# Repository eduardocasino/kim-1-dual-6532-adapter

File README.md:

# KIM-1 Dual 6530-6532 adapter

## Introduction

Welcome to the KIM-1 Dual 6530-6532 adapter repository. This adapter replaces both 6530 chips on the KIM-1 with a single board that contains a couple of 6532 chips, an EPROM and a few logic ICs.

As far as I know, this is the only board that allows you to replace both 6530 chips simultaneously.

## About

I designed this board for [my KIM-1 PCB replica](https://github.com/eduardocasino/kim-1), but it will also work with real KIM-1s that have both RRIOTs missing or broken.

The schematic is based on Ruud Baltissen's KIM-1 replica, with very minor modifications. The PCB features hand-traced tracks to seamlessly integrate with the KIM-1 board:

~~WARNING: I have not yet sent the board to fabrication, so it is untested!~~

The board has been successfully tested with my [my KIM-1 replica](https://github.com/eduardocasino/kim-1)

## Programming the EPROM

You can get the ROM contents from [Hans Otten's site](http://retro.hansotten.nl/6502-sbc/kim-1-manuals-and-software/kim_1-roms/)

There are two sets available: One that uses $00 as filler bytes and another that uses $FF. Both work equally well, but the one with $00 is what the original KIM-1 has. To program the EPROM:

1. Download "6530-002 fillerbyte00.bin" and "6530-003 fillerbyte00.bin" from Hans Otten's site (replace FF with 00 if you wish)
"6530-003 fillerbyte00.bin" has the ROM contents from $1800 to $1BFF and
"6530-002 fillerbyte00.bin" from $1C00 to $1FFF

2. Concat both files:

~~~
$ cat "6530-003 fillerbyte00.bin" "6530-002 fillerbyte00.bin" > KIM-1-ROM.bin
~~~

3. Program the EPROM with the resulting file starting at address $1800

## Licensing

This is a personal project that I am sharing in case it is of interest to any retrocomputing enthusiast and all the information in this repository is provided "as is", without warranty of any kind. I am not liable for any damages that may occur, whether it be to individuals, objects, KIM-1 computers, kittens or any other pets. It should also be noted that this design has not been tested and may contain errors, therefore anyone who chooses to use it does so at their own risk.

This work is licensed under a [Creative Commons Attribution-NonCommercial 4.0 International License](http://creativecommons.org/licenses/by-nc/4.0/).

EXCEPTION: The electrical schematic and all the associated symbols are licensed under a [Creative Commons Attribution 4.0 International License](https://creativecommons.org/licenses/by/4.0/).

See the LICENSE.md file for details.

## Changelog
#### 05/05/2023
* Fix tracks that were not well imported from svg
#### 09/04/2023
* Make ROM content available on phi2 only
* Add decoupling capacitor to ROM chip

## Acknowledgements

* Hans Otten and his [Retro Computing blog](http://retro.hansotten.nl/). Everything you need to know about the RRIOT and RIOT.
* Ruud Baltissen for [the original schematic](http://www.baltissen.org/newhtm/buildkim.htm).
* Frank Wolf and Dieter a.k.a. ttlworks for their [6530-004 dissection](http://forum.6502.org/viewtopic.php?f=4&t=6711) (Also [here](http://retro.hansotten.nl/6502-sbc/tim-6530-004/6530-004-dissected/)).

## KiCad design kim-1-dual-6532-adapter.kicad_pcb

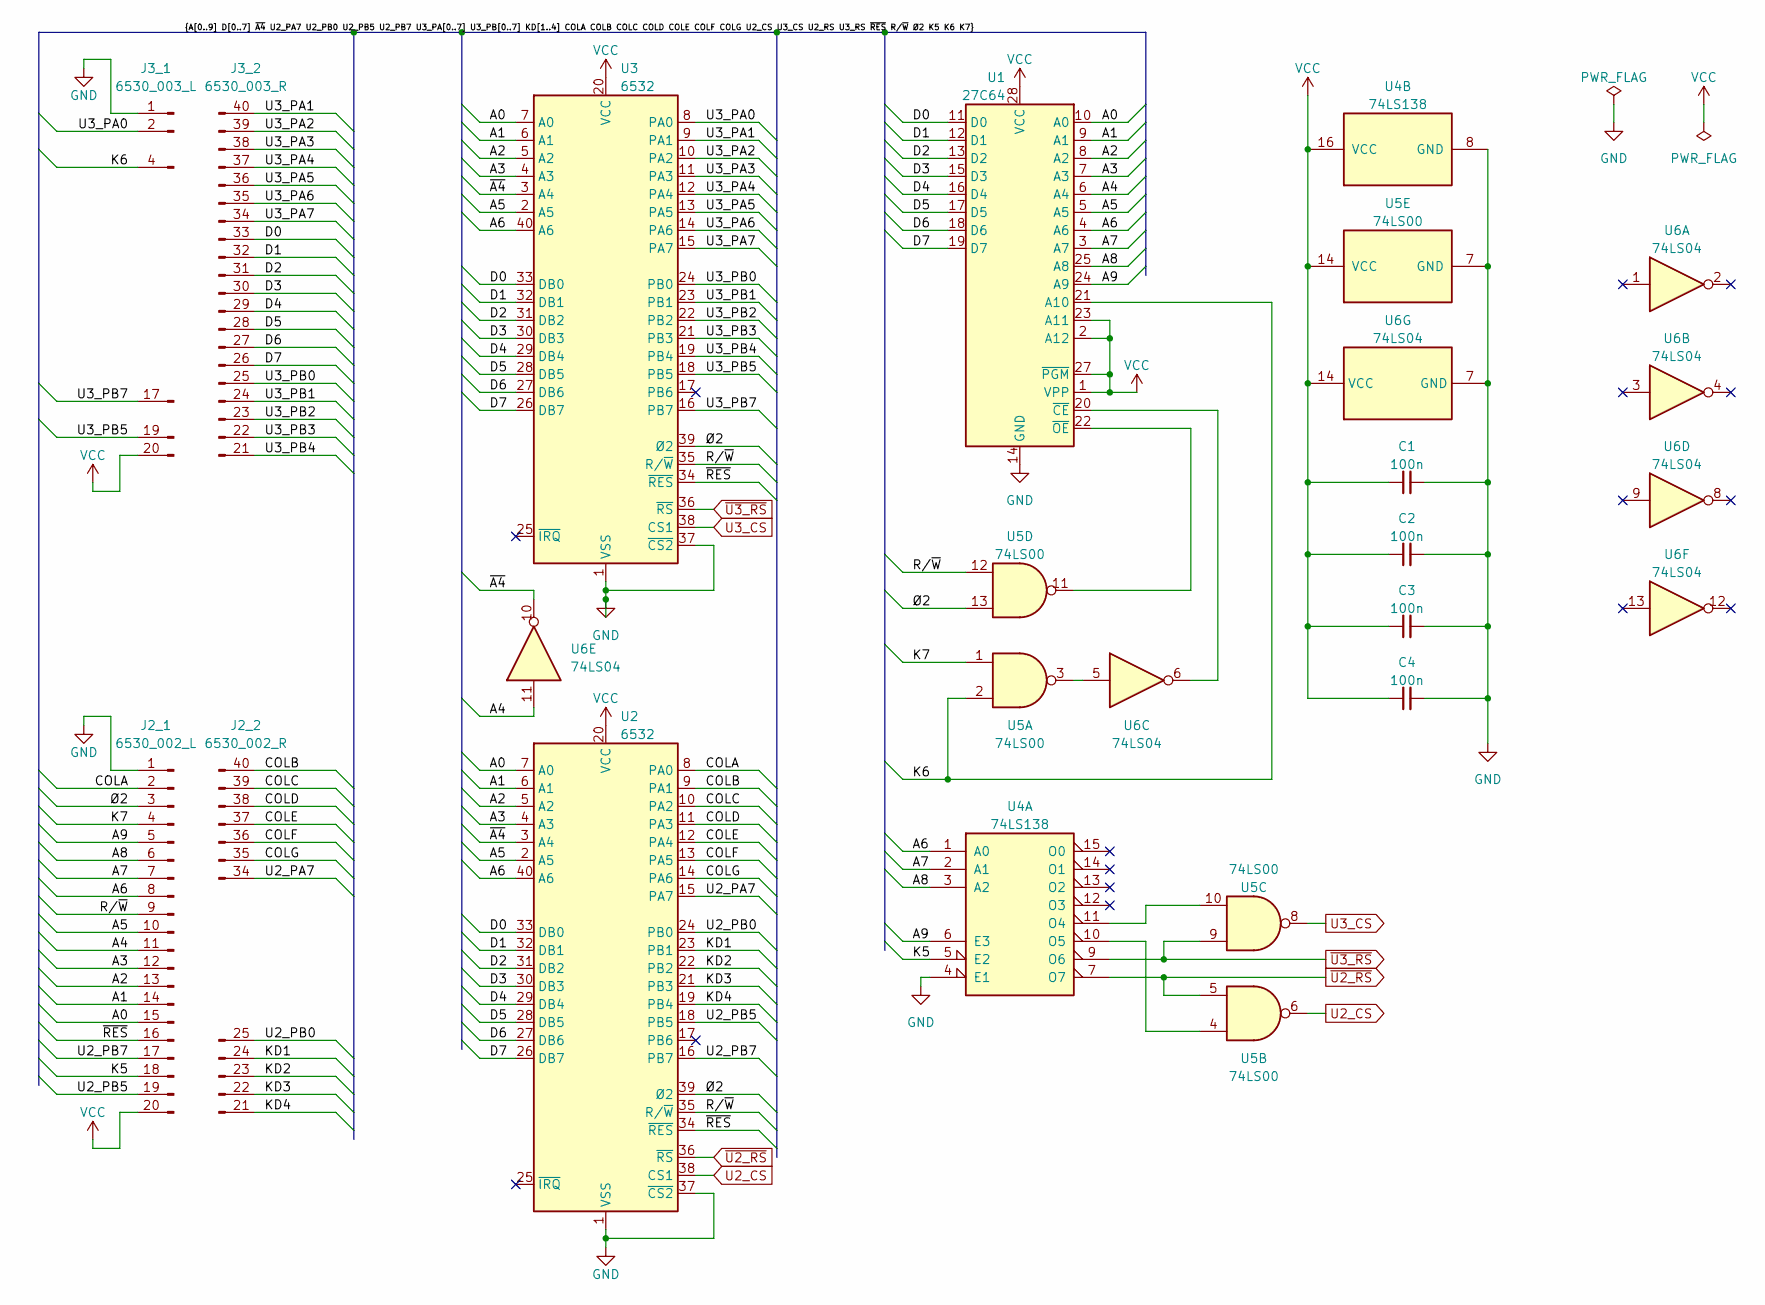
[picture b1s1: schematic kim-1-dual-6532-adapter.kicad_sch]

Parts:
C1, C2, C3, C4: 100n; C_Disc_D3.0mm_W2.0mm_P2.50mm
J2_1: 6530_002_L; PinHeader_1x20_A_P2.54mm_Vertical
J2_2: 6530_002_R; PinHeader_1x20_D_P2.54mm_Vertical
J3_1: 6530_003_L; PinHeader_1x20_C_P2.54mm_Vertical
J3_2: 6530_003_R; PinHeader_1x20_B_P2.54mm_Vertical
U1: 27C64; DIP-28_W15.24mm
U2, U3: 6532; DIP-40_W15.24mm
U4: 74LS138; DIP-16_W7.62mm
U5: 74LS00; DIP-14_W7.62mm
U6: 74LS04; DIP-14_W7.62mm

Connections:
/A0: J2_1.15, U1.10 (A0), U2.7 (A0), U3.7 (A0)
/A1: J2_1.14, U1.9 (A1), U2.6 (A1), U3.6 (A1)
/A2: J2_1.13, U1.8 (A2), U2.5 (A2), U3.5 (A2)
/A3: J2_1.12, U1.7 (A3), U2.4 (A3), U3.4 (A3)
/A4: J2_1.11, U1.6 (A4), U6.11
/A5: J2_1.10, U1.5 (A5), U2.2 (A5), U3.2 (A5)
/A6: J2_1.8, U1.4 (A6), U2.40 (A6), U3.40 (A6), U4.1 (A0)
/A7: J2_1.7, U1.3 (A7), U4.2 (A1)
/A8: J2_1.6, U1.25 (A8), U4.3 (A2)
/A9: J2_1.5, U1.24 (A9), U4.6 (E3)
/COLA: J2_1.2, U2.8 (PA0)
/COLB: J2_2.40, U2.9 (PA1)
/COLC: J2_2.39, U2.10 (PA2)
/COLD: J2_2.38, U2.11 (PA3)
/COLE: J2_2.37, U2.12 (PA4)
/COLF: J2_2.36, U2.13 (PA5)
/COLG: J2_2.35, U2.14 (PA6)
/D0: J3_2.33, U1.11 (D0), U2.33 (DB0), U3.33 (DB0)
/D1: J3_2.32, U1.12 (D1), U2.32 (DB1), U3.32 (DB1)
/D2: J3_2.31, U1.13 (D2), U2.31 (DB2), U3.31 (DB2)
/D3: J3_2.30, U1.15 (D3), U2.30 (DB3), U3.30 (DB3)
/D4: J3_2.29, U1.16 (D4), U2.29 (DB4), U3.29 (DB4)
/D5: J3_2.28, U1.17 (D5), U2.28 (DB5), U3.28 (DB5)
/D6: J3_2.27, U1.18 (D6), U2.27 (DB6), U3.27 (DB6)
/D7: J3_2.26, U1.19 (D7), U2.26 (DB7), U3.26 (DB7)
/K5: J2_1.18, U4.5 (E2)
/K6: J3_1.4, U1.21 (A10), U5.2
/K7: J2_1.4, U5.1
/KD1: J2_2.24, U2.23 (PB1)
/KD2: J2_2.23, U2.22 (PB2)
/KD3: J2_2.22, U2.21 (PB3)
/KD4: J2_2.21, U2.19 (PB4)
/R/~W: J2_1.9, U2.35 (R/~W), U3.35 (R/~W), U5.12
/U2_PA7: J2_2.34, U2.15 (PA7)
/U2_PB0: J2_2.25, U2.24 (PB0)
/U2_PB5: J2_1.19, U2.18 (PB5)
/U2_PB7: J2_1.17, U2.16 (PB7)
/U3_PA0: J3_1.2, U3.8 (PA0)
/U3_PA1: J3_2.40, U3.9 (PA1)
/U3_PA2: J3_2.39, U3.10 (PA2)
/U3_PA3: J3_2.38, U3.11 (PA3)
/U3_PA4: J3_2.37, U3.12 (PA4)
/U3_PA5: J3_2.36, U3.13 (PA5)
/U3_PA6: J3_2.35, U3.14 (PA6)
/U3_PA7: J3_2.34, U3.15 (PA7)
/U3_PB0: J3_2.25, U3.24 (PB0)
/U3_PB1: J3_2.24, U3.23 (PB1)
/U3_PB2: J3_2.23, U3.22 (PB2)
/U3_PB3: J3_2.22, U3.21 (PB3)
/U3_PB4: J3_2.21, U3.19 (PB4)
/U3_PB5: J3_1.19, U3.18 (PB5)
/U3_PB7: J3_1.17, U3.16 (PB7)
/~A4: U2.3 (A4), U3.3 (A4), U6.10
/~RES: J2_1.16, U2.34 (~RES), U3.34 (~RES)
/Ø2: J2_1.3, U2.39 (Ø2), U3.39 (Ø2), U5.13
GND: C1.2, C2.2, C3.2, C4.2, J2_1.1, J3_1.1, U1.14 (GND), U2.1 (VSS), U2.37 (~CS2), U3.1 (VSS), U3.37 (~CS2), U4.4 (E1), U4.8 (GND), U5.7 (GND), U6.7 (GND)
unnamed: U1.20 (~CE), U6.6
unnamed: U1.22 (~OE), U5.11
unnamed: U4.11 (O4), U5.10
unnamed: U4.10 (O5), U5.4
unnamed: U5.3, U6.5
U2_CS: U2.38 (CS1), U5.6
U3_CS: U3.38 (CS1), U5.8
VCC: C1.1, C2.1, C3.1, C4.1, J2_1.20, J3_1.20, U1.1 (VPP), U1.2 (A12), U1.23 (A11), U1.27 (~PGM), U1.28 (VCC), U2.20 (VCC), U3.20 (VCC), U4.16 (VCC), U5.14 (VCC), U6.14 (VCC)
~U2_RS: U2.36 (~RS), U4.7 (O7), U5.5
~U3_RS: U3.36 (~RS), U4.9 (O6), U5.9

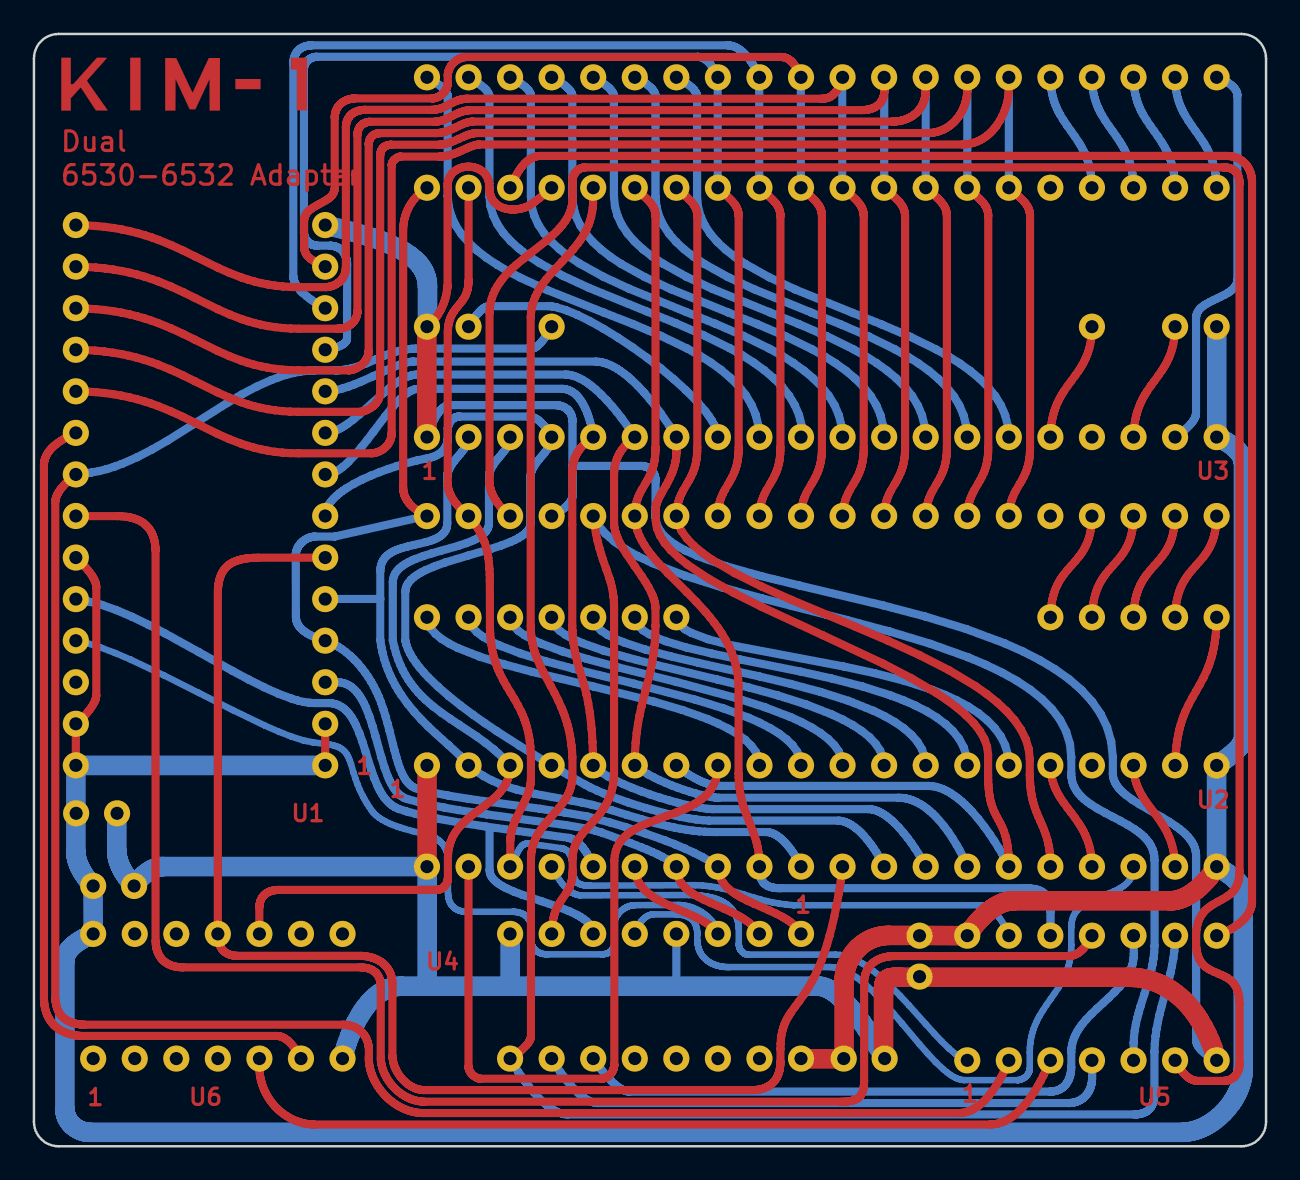
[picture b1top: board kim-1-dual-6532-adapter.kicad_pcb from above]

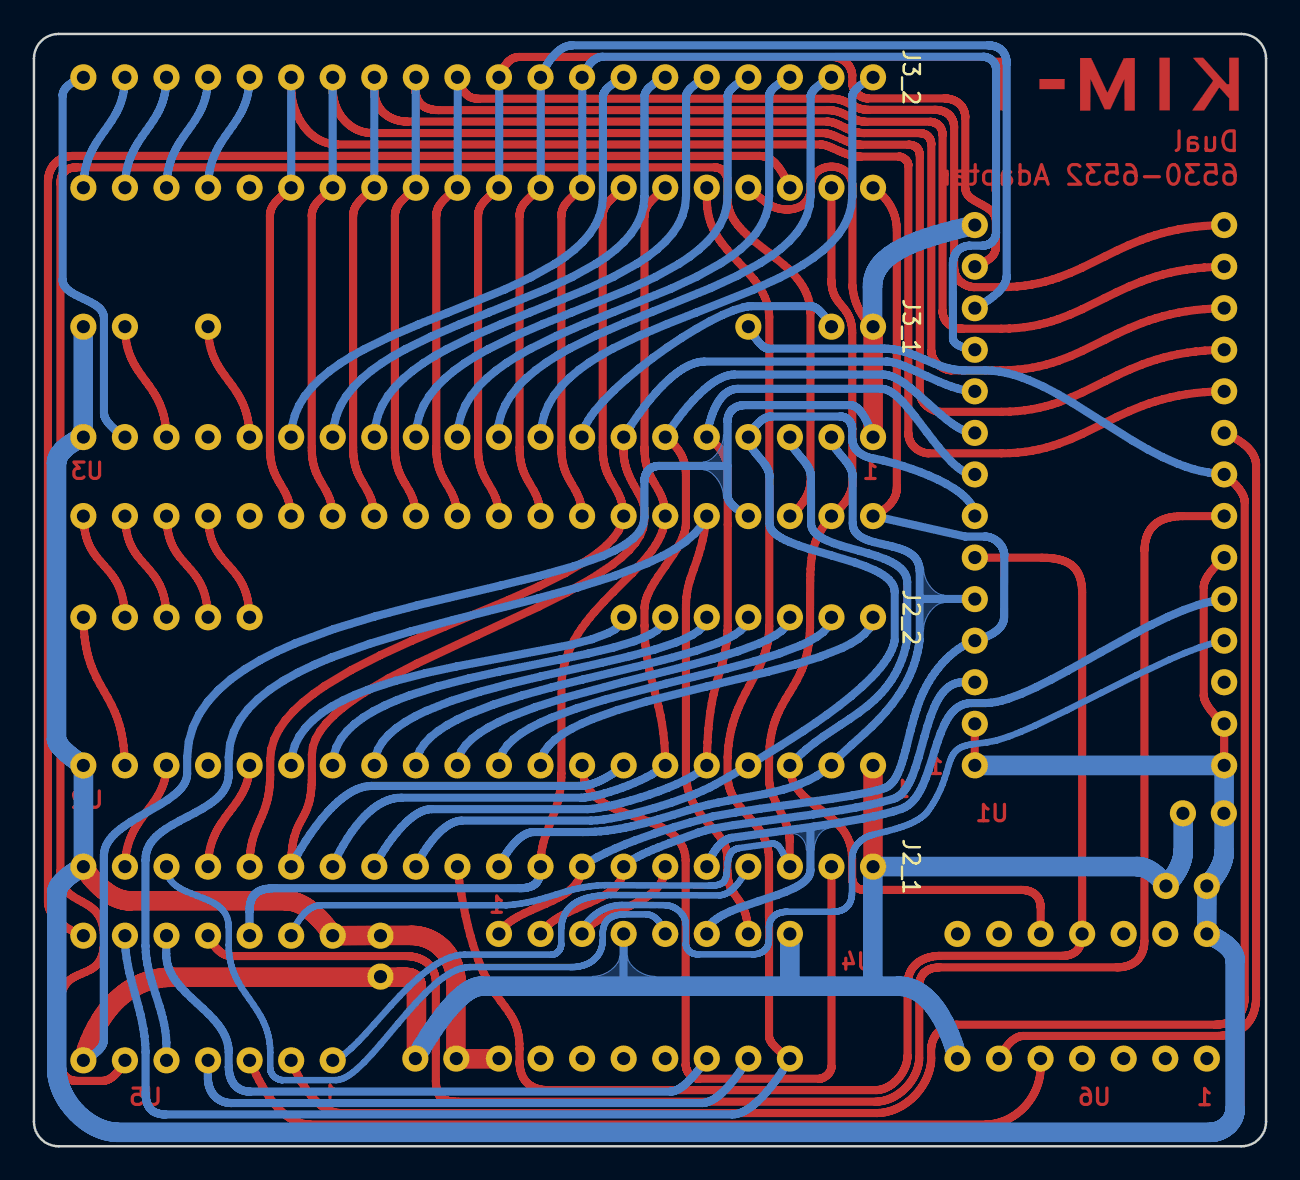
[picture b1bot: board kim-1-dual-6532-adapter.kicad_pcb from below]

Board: 2 copper layers, 75.3 x 68.0 mm, 15 parts (4 on the bottom side), 66 nets.

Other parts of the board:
Ref**: Val**; KIM-1_Logo

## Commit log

2023-04-04 Fix copy-paste mistake
2023-04-04 Typo
2023-04-05 Adjust some references
2023-04-05 Another typo
2023-04-09 Control ROM's OE with phi2
2023-04-09 Add a changelog
2023-05-05 Fix tracks that were not well imported from svg
2023-05-25 Generate correct gerber files format
2023-08-03 Update board status
2023-11-19 Add instructions for programming the EPROM. Fixes #1

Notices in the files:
README.md:
Licensing:
[CC BY-NC 4.0](http://creativecommons.org/licenses/by-nc/4.0/)
Th
